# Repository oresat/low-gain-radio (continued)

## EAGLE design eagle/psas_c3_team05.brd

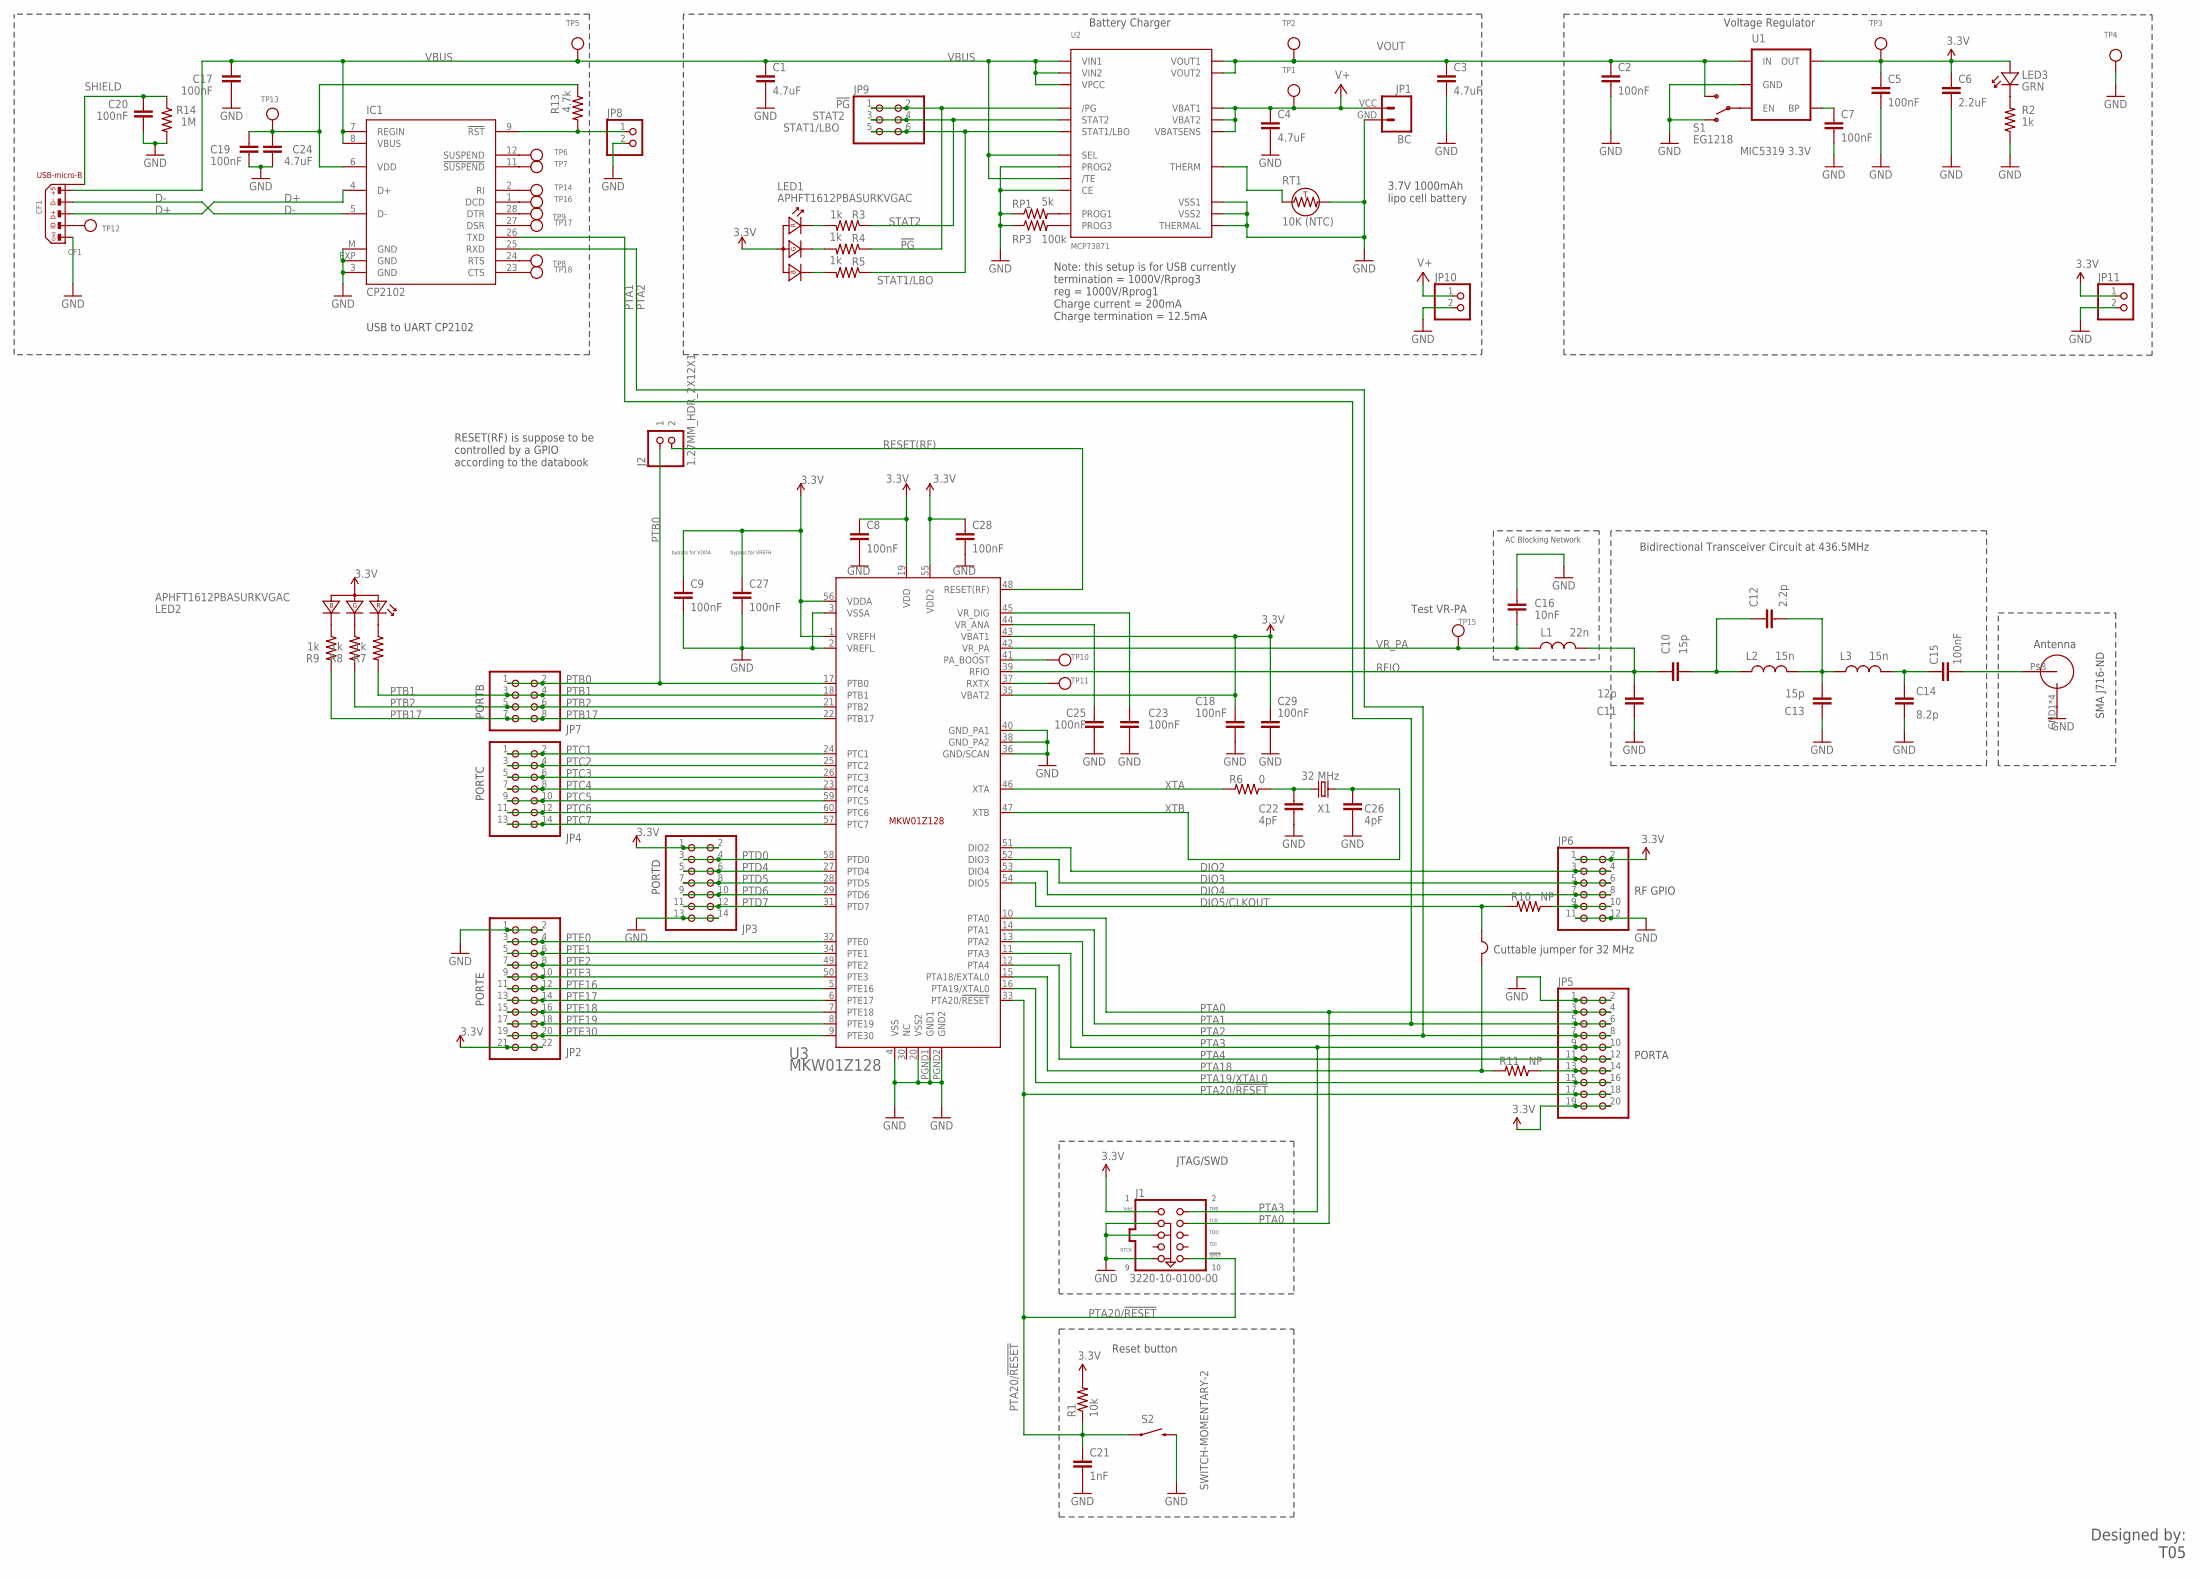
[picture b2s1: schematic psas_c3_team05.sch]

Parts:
C1, C3, C4, C24: 4.7uF; .0805-B-NOSILK
C2, C5, C7, C15, C17, C19, C20: 100nF; .0603-B-NOSILK
C6: 2.2uF; .0805-B-NOSILK
C8, C9, C18, C23, C25, C27, C28, C29: 100nF; .0603-B-NOSILK; MPN GRM188R71C104KA01D
C10, C13: 15p; .0603-B-NOSILK
C11: 12p; .0603-B-NOSILK
C12: 2.2p; .0603-B-NOSILK
C14: 8.2p; .0603-B-NOSILK
C16: 10nF; .0603-B-NOSILK
C21: 1nF; .0603-B-NOSILK
C22, C26: 4pF; .0603-B-NOSILK; MPN GRM1885C1H4R0CA01D
CF1: CF1; USB-MICRO-B-PTH-HIROSE
IC1: CP2102; MLP28
J1: 3220-10-0100-00; PINHEADER-2X5-0.05+POL+SILK
J2: 1.27MM_HDR_2X12X1; 1.27MM_2X1
JP1: BC; SPARKFUN-CONNECTORS_JST-2-SMD-VERT
JP2: PINHD-2X11; 2X11
JP3, JP4: PINHD-2X7; 2X07
JP5: PINHD-2X10; 2X10
JP6: PINHD-2X6; 2X06
JP7: PINHD-2X4; 2X04
JP8, JP10, JP11: PINHD-1X2; 1X02
JP9: PINHD-2X3; 2X03
L1: 22n; .0603-B-NOSILK
L2, L3: 15n; .0603-B-NOSILK
LED1, LED2: APHFT1612PBASURKVGAC; KINGBRITE_RGBLED_1.6X1.26
LED3: GRN; LED-0603
R1: 10k; .0603-B-NOSILK
R2, R3, R4, R5, R7, R8, R9: 1k; .0603-B-NOSILK
R6: 0; .0603-B-NOSILK
R10, R11: NP; .0603-B-NOSILK
R13: 4.7k; .0603-B-NOSILK
R14: 1M; .0603-B-NOSILK
RP1: 5k; .0603-B-NOSILK
RP3: 100k; .0603-B-NOSILK
RT1: 10K (NTC); R1206
S1: EG1218; SWITCH-SPDT
S2: SWITCH-MOMENTARY-2; TACTILE_SWITCH_TALL
TP1, TP2, TP3, TP4, TP5, TP6, TP7, TP8, TP9, TP10, TP11, TP12, TP13, TP14, TP15, TP16, TP17, TP18: TESTPOINTROUND0.5MM; TESTPOINT_ROUND_0.5MM
U1: MIC5319 3.3V; SPARKFUN-POWERIC_SOT23-5
U2: MCP73871; QFN20_4MM
U3: MKW01Z128
U$2: SMAJ716-ND
W1: CONNECTION-0.4; CONNECTION-BUTT-0.4
X1: 32 MHz; FC-12M

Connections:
3.3V: C5.1, C6.1, C8.1, C9.1, C18.1, C27.1, C28.1, C29.1, J1.1 (VDD), JP2.21, JP2.22, JP3.1, JP3.2, JP5.19, JP5.20, JP6.1, JP6.2, JP11.1, LED1.2 (COMMON_ANODE), LED2.2 (COMMON_ANODE), LED3.A, R1.2, TP3.P$1, U1.5 (OUT), U3.1 (VREFH), U3.19 (VDD), U3.35 (VBAT2), U3.43 (VBAT1), U3.55 (VDD2), U3.56 (VDDA)
!PG: JP9.1, JP9.2, R4.1, U2.P$6 (/PG)
CP2102_VDD: C19.1, C24.1, IC1.6 (VDD), R13.1, TP13.P$1
D+: CF1.3, IC1.4 (D+)
D-: CF1.2, IC1.5 (D-)
DIO2: JP6.3, JP6.4, U3.51 (DIO2)
DIO3: JP6.5, JP6.6, U3.52 (DIO3)
DIO4: JP6.7, JP6.8, U3.53 (DIO4)
DIO5-JMP: JP6.9, JP6.10, R10.1
DIO5/CLKOUT: R10.2, U3.54 (DIO5), W1.P1 (1)
GND: C1.2, C2.2, C3.2, C4.2, C5.2, C6.2, C7.2, C8.2, C9.2, C11.2, C13.2, C14.2, C16.1, C17.2, C18.2, C19.2, C20.2, C21.2, C22.2, C23.2, C24.2, C25.2, C26.2, C27.2, C28.2, C29.2, CF1.5, IC1.3 (GND), IC1.EXP (GND), IC1.M (GND), J1.3 (GND3), J1.5 (GND5), J1.9 (GND9), JP1.GND (1), JP2.1, JP2.2, JP3.13, JP3.14, JP5.1, JP5.2, JP6.11, JP6.12, JP8.2, JP10.2, JP11.2, R2.1, R14.2, RP1.1, RP3.1, RT1.2, S1.1 (O), S2.B2 (2), TP4.P$1, U1.2 (GND), U2.P$4 (PROG2), U2.P$10 (VSS1), U2.P$11 (VSS2), U2.P$17 (CE), U2.P$21 (THERMAL), U3.2 (VREFL), U3.3 (VSSA), U3.4 (VSS), U3.20 (VSS2), U3.36 (GND/SCAN), U3.38 (GND_PA2), U3.40 (GND_PA1), U3.PGND1 (GND1), U3.PGND2 (GND2), U$2.GND1 (OUTERCONDUCTOR), U$2.GND2 (OUTERCONDUCTOR), U$2.GND3 (OUTERCONDUCTOR), U$2.GND4 (OUTERCONDUCTOR)
unnamed: C7.1, U1.4 (BP)
unnamed: LED1.3 (RK), R3.2
unnamed: LED1.4 (GK), R4.2
unnamed: LED1.1 (BK), R5.2
unnamed: IC1.12 (SUSPEND), TP6.P$1
unnamed: RT1.1, U2.P$5 (THERM)
unnamed: IC1.11 (!SUSPEND), TP7.P$1
unnamed: S1.2, U1.3 (EN)
unnamed: RP1.2, U2.P$13 (PROG1)
unnamed: RP3.2, U2.P$12 (PROG3)
unnamed: IC1.24 (RTS), TP8.P$1
unnamed: C22.1, R6.1, X1.2
unnamed: TP10.P$1, U3.41 (PA_BOOST)
unnamed: TP11.P$1, U3.37 (RXTX)
unnamed: C12.1, C13.1, L2.2, L3.1
unnamed: C10.1, C12.2, L2.1
unnamed: C15.2, U$2.P$3 (CENTERCONDUCTOR)
unnamed: C14.1, C15.1, L3.2
unnamed: IC1.2 (RI), TP14.P$1
unnamed: IC1.28 (DTR), TP9.P$1
unnamed: IC1.1 (DCD), TP16.P$1
unnamed: IC1.27 (DSR), TP17.P$1
unnamed: IC1.23 (CTS), TP18.P$1
unnamed: IC1.9 (!RST), JP8.1, R13.2
unnamed: LED3.K, R2.2
unnamed: LED2.1 (BK), R9.1
unnamed: LED2.4 (GK), R8.1
unnamed: LED2.3 (RK), R7.1
unnamed: CF1.4, TP12.P$1
PTA0: J1.4 (TCK), JP5.3, JP5.4, U3.10 (PTA0)
PTA1: IC1.26 (TXD), JP5.5, JP5.6, U3.14 (PTA1)
PTA2: IC1.25 (RXD), JP5.7, JP5.8, U3.13 (PTA2)
PTA3: J1.2 (TMS), JP5.9, JP5.10, U3.11 (PTA3)
PTA4: JP5.11, JP5.12, U3.12 (PTA4)
PTA18: R11.2, U3.15 (PTA18/EXTAL0), W1.P2 (2)
PTA18-JMP: JP5.13, JP5.14, R11.1
PTA19/XTAL0: JP5.15, JP5.16, U3.16 (PTA19/XTAL0)
PTA20/!RESET: C21.1, J1.10 (SRST), JP5.17, JP5.18, R1.1, S2.A2 (1), U3.33 (PTA20/!RESET)
PTB0: J2.1, JP7.1, JP7.2, U3.17 (PTB0)
PTB1: JP7.3, JP7.4, R7.2, U3.18 (PTB1)
PTB2: JP7.5, JP7.6, R8.2, U3.21 (PTB2)
PTB17: JP7.7, JP7.8, R9.2, U3.22 (PTB17)
PTC1: JP4.1, JP4.2, U3.24 (PTC1)
PTC2: JP4.3, JP4.4, U3.25 (PTC2)
PTC3: JP4.5, JP4.6, U3.26 (PTC3)
PTC4: JP4.7, JP4.8, U3.23 (PTC4)
PTC5: JP4.9, JP4.10, U3.59 (PTC5)
PTC6: JP4.11, JP4.12, U3.60 (PTC6)
PTC7: JP4.13, JP4.14, U3.57 (PTC7)
PTD0: JP3.3, JP3.4, U3.58 (PTD0)
PTD4: JP3.5, JP3.6, U3.27 (PTD4)
PTD5: JP3.7, JP3.8, U3.28 (PTD5)
PTD6: JP3.9, JP3.10, U3.29 (PTD6)
PTD7: JP3.11, JP3.12, U3.31 (PTD7)
PTE0: JP2.3, JP2.4, U3.32 (PTE0)
PTE1: JP2.5, JP2.6, U3.34 (PTE1)
PTE2: JP2.7, JP2.8, U3.49 (PTE2)
PTE3: JP2.9, JP2.10, U3.50 (PTE3)
PTE16: JP2.11, JP2.12, U3.5 (PTE16)
PTE17: JP2.13, JP2.14, U3.6 (PTE17)
PTE18: JP2.15, JP2.16, U3.7 (PTE18)
PTE19: JP2.17, JP2.18, U3.8 (PTE19)
PTE30: JP2.19, JP2.20, U3.9 (PTE30)
RESET(RF): J2.2, U3.48 (RESET(RF))
RFIO: C10.2, C11.1, L1.2, U3.39 (RFIO)
SHIELD: C20.1, CF1.S1 (SHIELD), CF1.S2 (SHIELD), CF1.S3 (SHIELD), CF1.S4 (SHIELD), R14.1
STAT1/LBO: JP9.5, JP9.6, R5.1, U2.P$8 (STAT1/LBO)
STAT2: JP9.3, JP9.4, R3.1, U2.P$7 (STAT2)
V+: C4.1, JP1.VCC (2), JP10.1, TP1.P$1, U2.P$14 (VBAT1), U2.P$15 (VBAT2), U2.P$16 (VBATSENS)
VBUS: C1.1, C17.1, CF1.1, IC1.7 (REGIN), IC1.8 (VBUS), TP5.P$1, U2.P$2 (VPCC), U2.P$3 (SEL), U2.P$9 (/TE), U2.P$18 (VIN1), U2.P$19 (VIN2)
VOUT: C2.1, C3.1, S1.3 (S), TP2.P$1, U1.1 (IN), U2.P$1 (VOUT1), U2.P$20 (VOUT2)
VR_ANA: C25.1, U3.44 (VR_ANA)
VR_DIG: C23.1, U3.45 (VR_DIG)
VR_PA: C16.2, L1.1, TP15.P$1, U3.42 (VR_PA)
XTA: R6.2, U3.46 (XTA)
XTB: C26.1, U3.47 (XTB), X1.1

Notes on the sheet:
Note: this setup is for USB currently termination = 1000V/Rprog3 reg = 1000V/Rprog1 Charge current = 200mA Charge termination = 12.5mA
Voltage Regulator
Battery Charger
Designed by: T05
AC Blocking Network
Bidirectional Transceiver Circuit at 436.5MHz
USB to UART CP2102
JTAG/SWD
Reset button
3.7V 1000mAh lipo cell battery
RESET(RF) is suppose to be controlled by a GPIO according to the databook
PORTC
PORTB
PORTD
PORTE
Cuttable jumper for 32 MHz
bypass for VDDA
bypass for VREFH
Antenna
SMA J716-ND
Test VR-PA
PORTA
RF GPIO

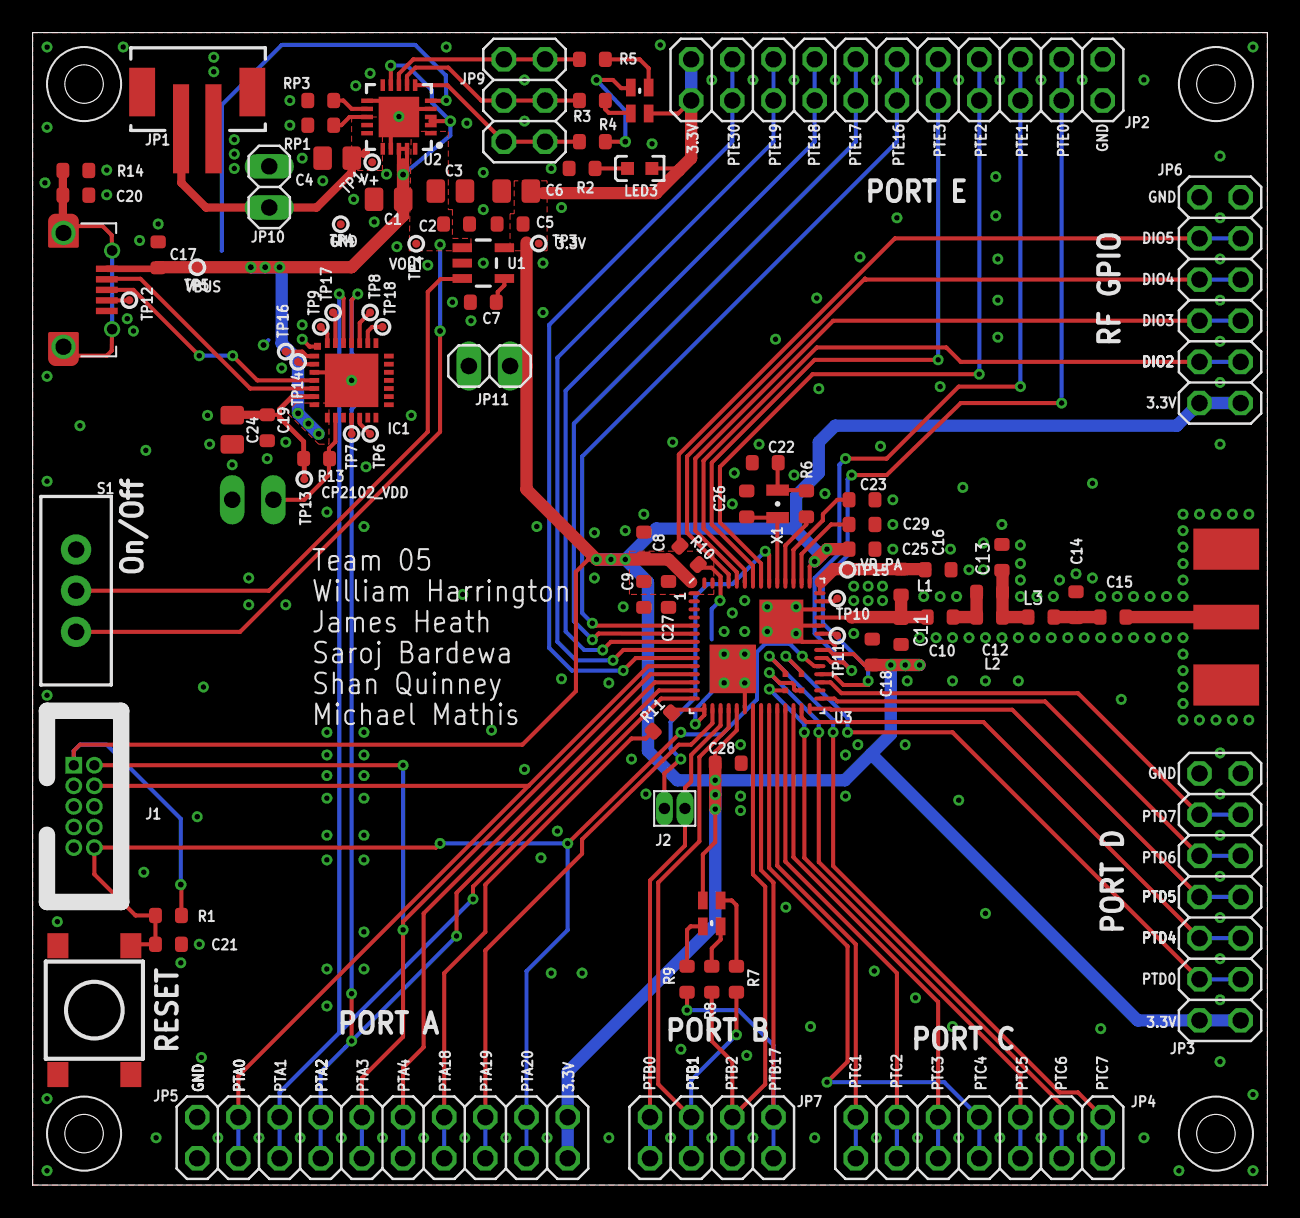
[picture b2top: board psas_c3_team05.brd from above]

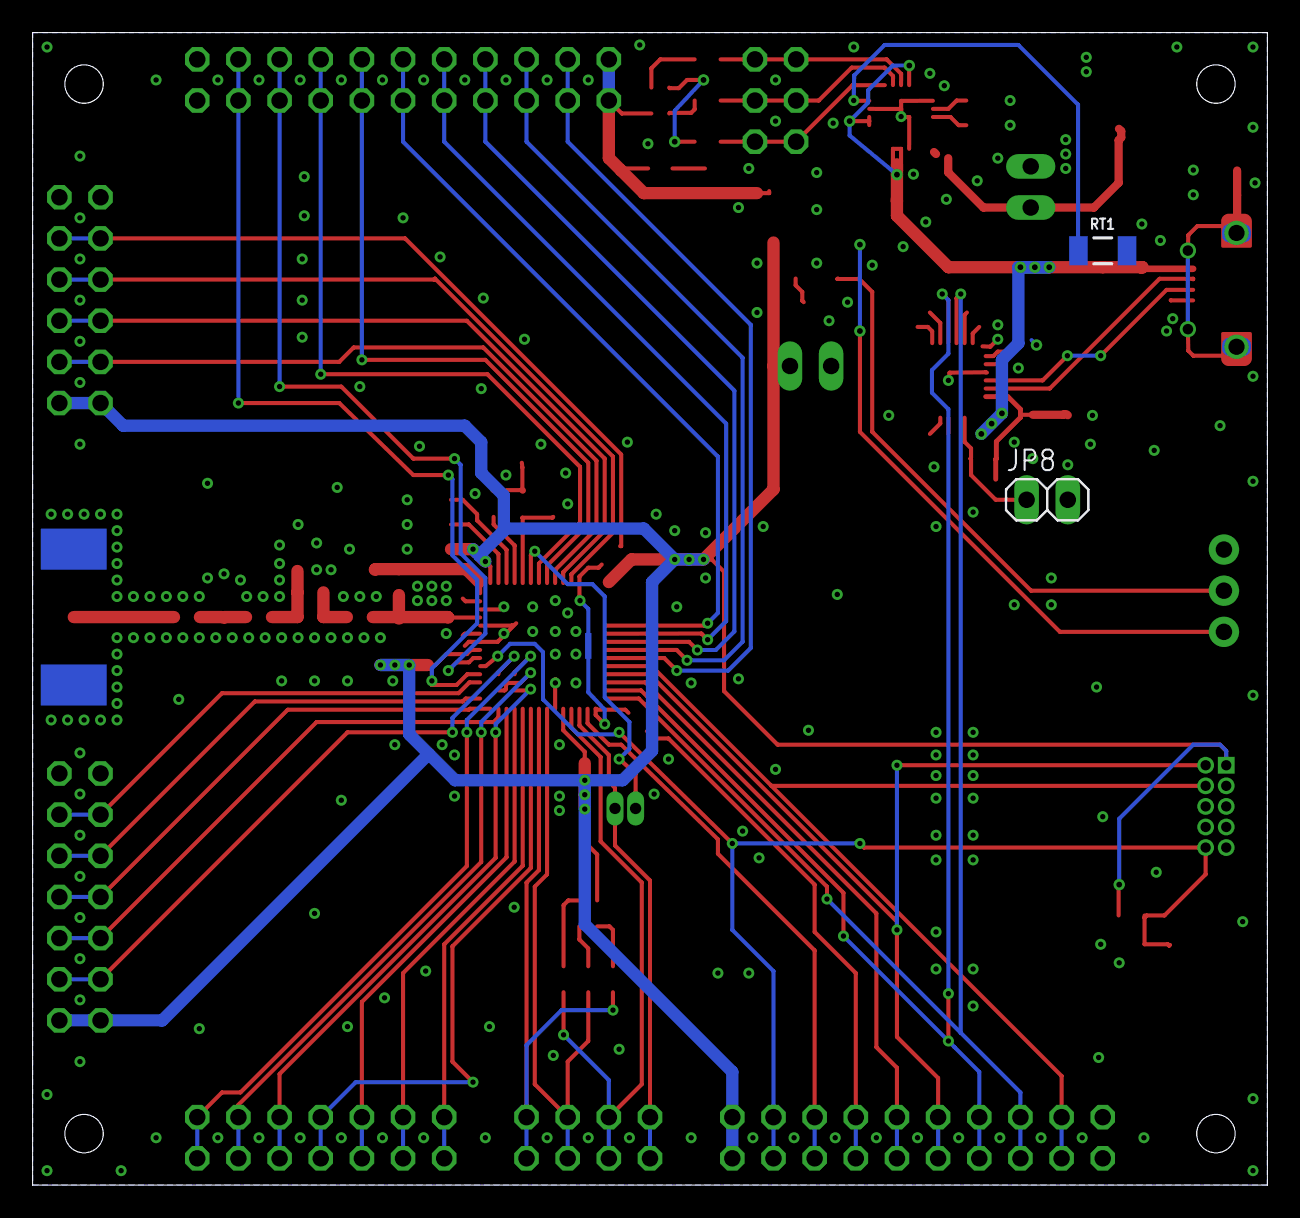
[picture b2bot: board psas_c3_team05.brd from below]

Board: 2 copper layers, 76.2 x 71.1 mm, 96 parts (3 on the bottom side), 87 nets.

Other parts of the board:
DI1, DI2, DI3, DI4: #2/.750-BARE

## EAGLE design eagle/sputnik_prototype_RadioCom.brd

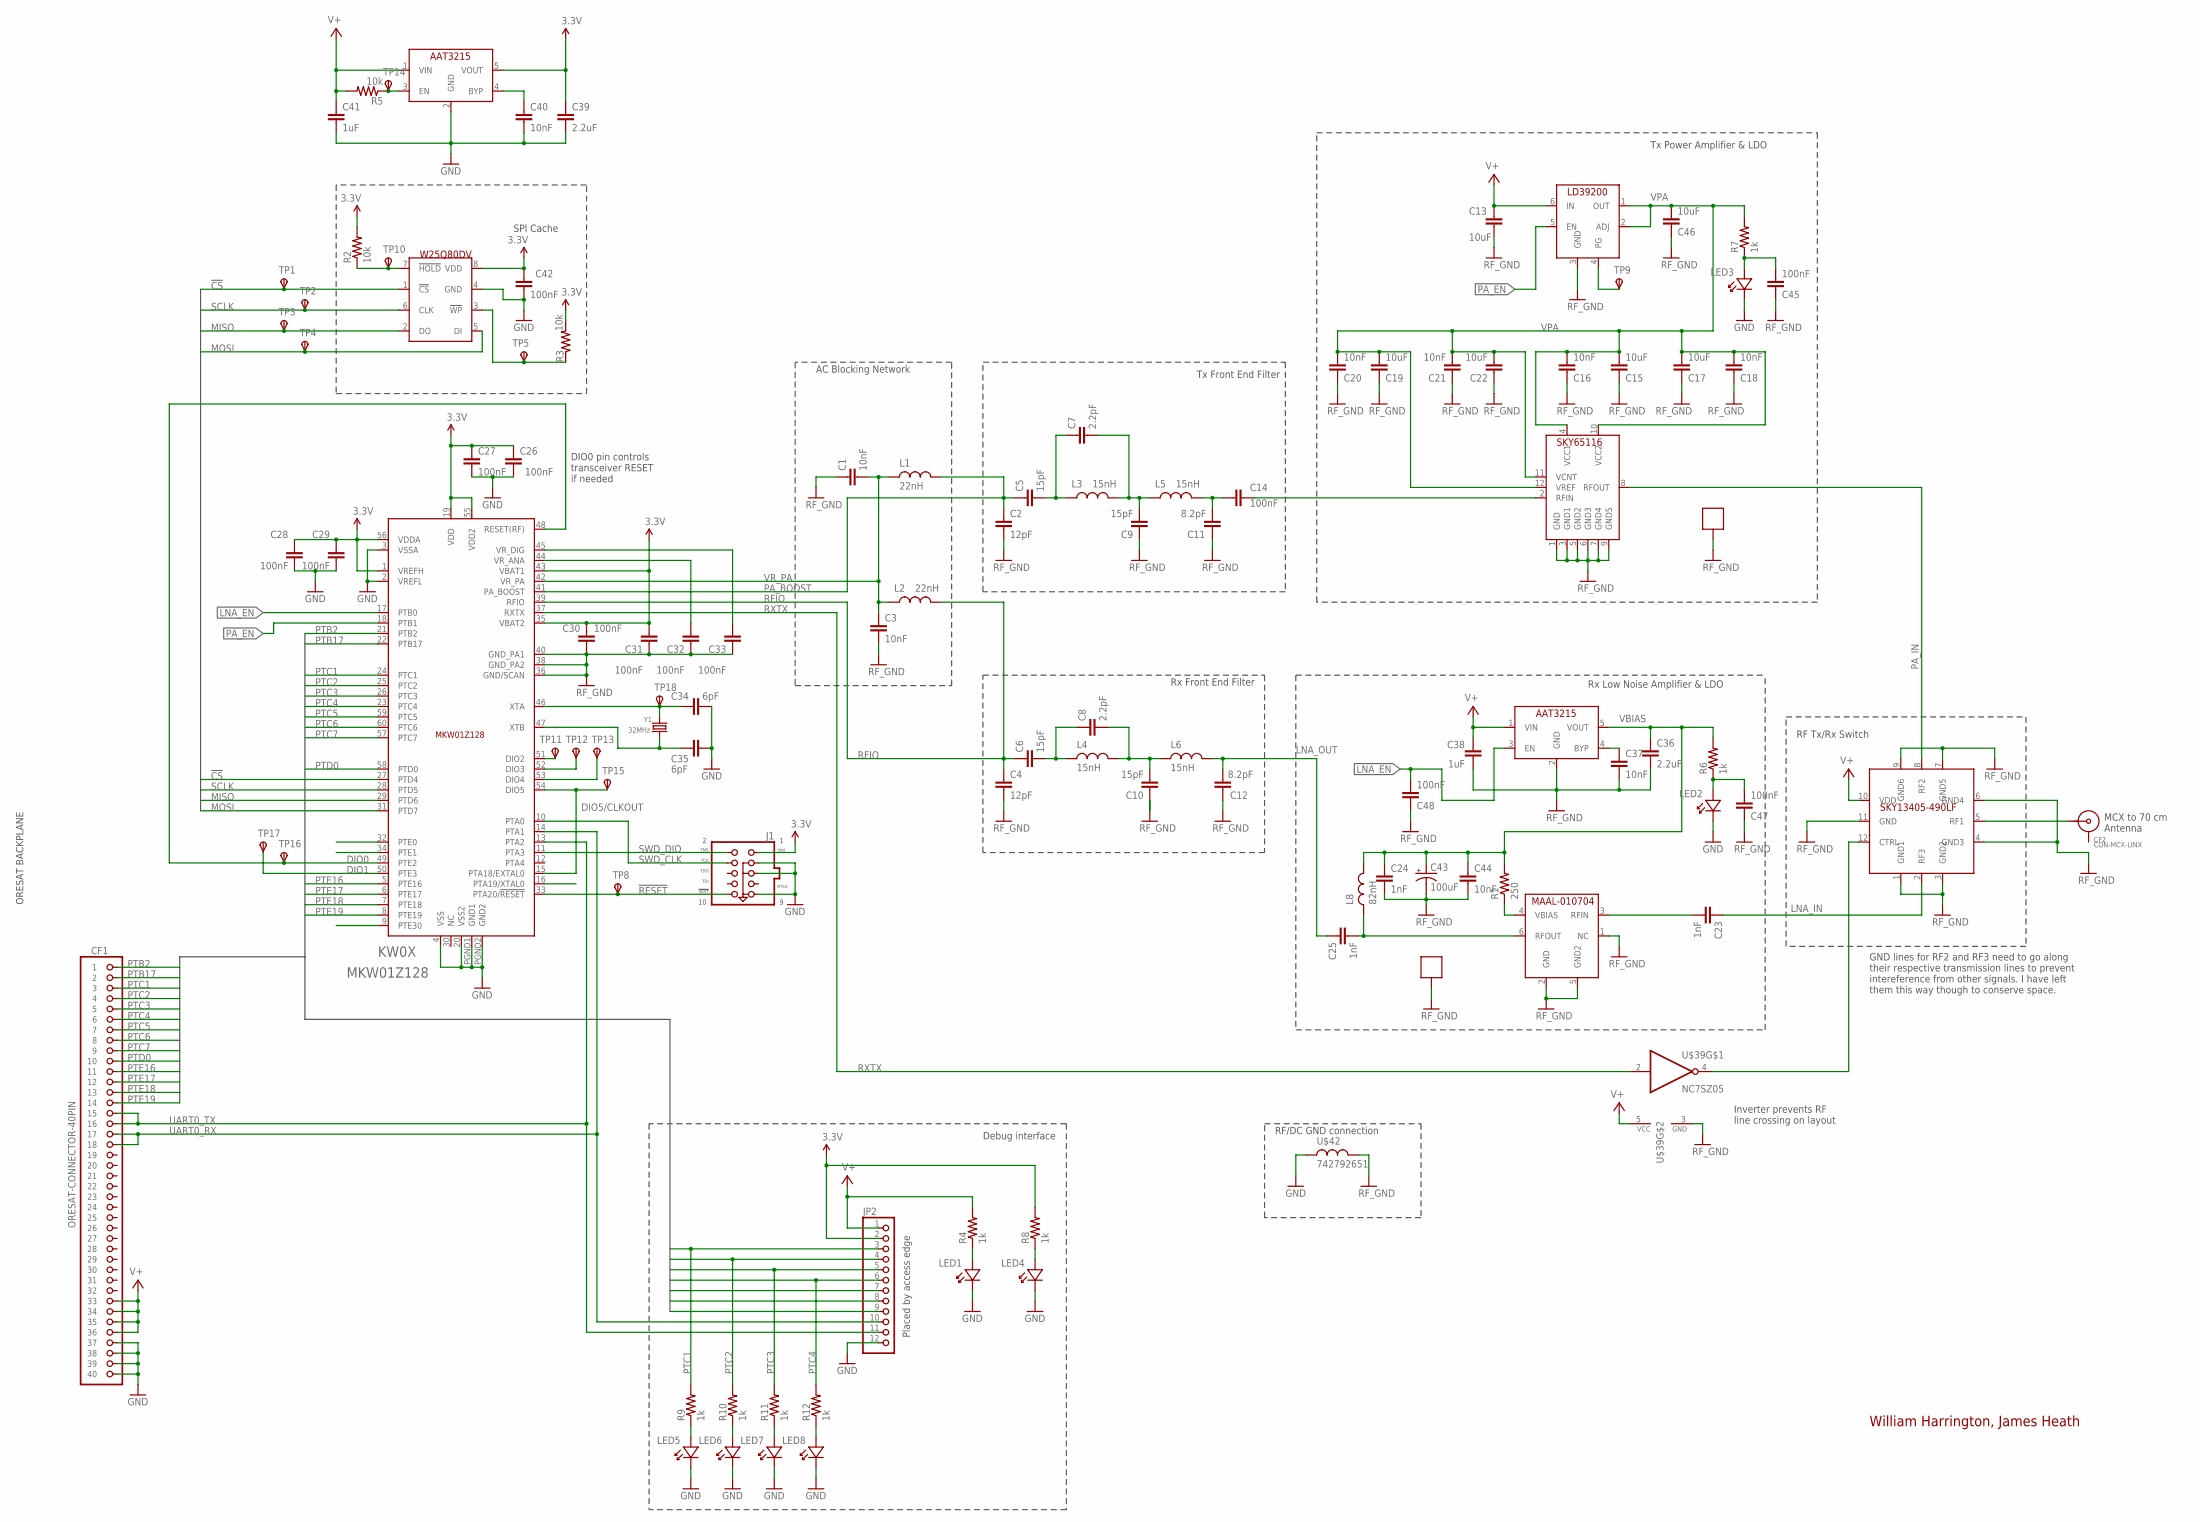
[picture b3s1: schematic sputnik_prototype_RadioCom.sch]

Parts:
C1, C3, C16, C18, C20, C21: 10nF; .0603-B-NOSILK
C2, C4: 12pF; .0603-B-NOSILK
C5, C6, C9, C10: 15pF; .0603-B-NOSILK
C7, C8: 2.2pF; .0603-B-NOSILK
C11, C12: 8.2pF; .0603-B-NOSILK
C13, C15, C17, C19, C22, C46: 10uF; .0603-B-NOSILK
C14, C26, C27, C28, C29, C30, C31, C32, C33, C42, C45, C47, C48: 100nF; .0603-B-NOSILK
C23, C24, C25: 1nF; .0402-B-NOSILK
C34, C35: 6pF; .0603-B-NOSILK
C36, C39: 2.2uF; .0402-B-NOSILK
C37, C40, C44: 10nF; .0402-B-NOSILK
C38, C41: 1uF; .0402-B-NOSILK
C43: 100uF; CT6032
CF1: ORESAT-CONNECTOR-40PIN; HARWIN-ARCHER-M50-3202045
CF2: CON-MCX-LINX; CON-MCX-LINX-CONMCX003.062
J1: JTAG_ARM-10-50MIL; PINHEADER-2X5-0.05+POL+SILK
JP2: PINHD-1X12; 1X12
KW0X: MKW01Z128; MPN MKW01Z128CHN
L1, L2: 22nH; .0603-B-NOSILK
L3, L4, L5, L6: 15nH; .0603-B-NOSILK
L8: 82nH; .0603-B-NOSILK
LED1, LED2, LED3, LED4, LED5, LED6, LED7, LED8: LED-0603
LNA: MAAL-010704; MPN MAAL-010704-TR3000
PA: SKY65116; MPN SKY65116
R1: 250; .0603-B-NOSILK
R2, R3, R5: 10k; .0603-B-NOSILK
R4, R6, R7, R8, R9, R10, R11, R12: 1k; .0603-B-NOSILK
SH1, SH2: BMI-S-202-SHIELD; BMI-S-202
TP1, TP2, TP3, TP4, TP5, TP8, TP9, TP10, TP11, TP12, TP13, TP14, TP15, TP16, TP17, TP18: TPSPAD1-13; P1-13
TRSWITCH: SKY13405-490LF; MPN SKY13405-490LF
U$1: W25Q80DV
U$7, U$8: AAT3215
U$9: LD39200
U$39: NC7SZ05
U$42: 742792651; .0603-B-NOSILK
Y1: 32MHz; CRYSTAL_2.5X2; MPN FA20H 32.0000MF12Y-W3

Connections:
3.3V: C26.1, C27.1, C28.2, C29.2, C30.2, C31.2, C39.1, C42.2, J1.1 (VDD), JP2.2, KW0X.1 (VREFH), KW0X.19 (VDD), KW0X.35 (VBAT2), KW0X.43 (VBAT1), KW0X.55 (VDD2), KW0X.56 (VDDA), R2.2, R3.2, R8.2, U$1.8 (VDD), U$8.5 (VOUT)
!CS: KW0X.27 (PTD4), TP1.TP, U$1.1 (!CS)
!HOLD: R2.1, TP10.TP, U$1.7 (!HOLD)
!RESET: J1.10 (SRST), KW0X.33 (PTA20/!RESET), TP8.TP
ASD: C47.1
DIO0: KW0X.48 (RESET(RF)), KW0X.49 (PTE2), TP16.TP
DIO1: KW0X.50 (PTE3), TP17.TP
DIO5/CLKOUT: KW0X.15 (PTA18/EXTAL0), KW0X.54 (DIO5), TP15.TP
GND: C26.2, C27.2, C28.1, C29.1, C34.1, C35.1, C36.2, C37.2, C38.2, C39.2, C40.2, C41.2, C42.1, C48.1, CF1.P$37 (37), CF1.P$38 (38), CF1.P$39 (39), CF1.P$40 (40), J1.3 (GND3), J1.5 (GND5), J1.9 (GND9), JP2.12, KW0X.2 (VREFL), KW0X.3 (VSSA), KW0X.4 (VSS), KW0X.20 (VSS2), KW0X.PGND1 (GND1), KW0X.PGND2 (GND2), LED1.K, LED2.K, LED3.K, LED4.K, LED5.K, LED6.K, LED7.K, LED8.K, LNA.1 (NC), TRSWITCH.11 (GND), U$1.4 (GND), U$7.2 (GND), U$8.2 (GND), U$42.1
LNA_EN: C48.2, KW0X.17 (PTB0), U$7.3 (EN)
LNA_IN: C23.1, TRSWITCH.2 (RF3)
LNA_OUT: C12.2, C25.1, L6.2
MISO: KW0X.29 (PTD6), TP3.TP, U$1.2 (DO)
MOSI: KW0X.31 (PTD7), TP4.TP, U$1.5 (DI)
unnamed: C37.1, U$7.4 (BYP)
unnamed: TRSWITCH.12 (CTRL), U$39.4 (OUT)
unnamed: KW0X.51 (DIO2), TP11.TP
unnamed: TP9.TP, U$9.4 (PG)
unnamed: KW0X.52 (DIO3), TP12.TP
unnamed: C34.2, KW0X.46 (XTA), TP18.TP, Y1.1
unnamed: C25.2, L8.1, LNA.6 (RFOUT)
unnamed: C35.2, KW0X.47 (XTB), Y1.3 (2)
unnamed: KW0X.53 (DIO4), TP13.TP
unnamed: C5.2, C7.1, L3.1
unnamed: R3.1, TP5.TP, U$1.3 (!WP)
unnamed: R5.1, TP14.TP, U$8.3 (EN)
unnamed: C40.1, U$8.4 (BYP)
unnamed: LED1.A, R4.1
unnamed: LED5.A, R9.1
unnamed: C7.2, C9.2, L3.2, L5.1
unnamed: C11.2, C14.2, L5.2
unnamed: C6.2, C8.1, L4.1
unnamed: C8.2, C10.2, L4.2, L6.1
unnamed: LED6.A, R10.1
unnamed: LED7.A, R11.1
unnamed: LED4.A, R8.1
unnamed: LED8.A, R12.1
unnamed: C23.2, LNA.3 (RFIN)
unnamed: LNA.4 (VBIAS), R1.1
unnamed: CF2.CENTER, TRSWITCH.5 (RF1)
unnamed: C32.2, KW0X.44 (VR_ANA)
unnamed: C33.2, KW0X.45 (VR_DIG)
unnamed: C14.1, PA.2 (RFIN)
PA_BOOST: C2.1, C5.1, KW0X.41 (PA_BOOST), L1.2
PA_EN: KW0X.18 (PTB1), U$9.5 (EN)
PA_IN: PA.8 (RFOUT), TRSWITCH.8 (RF2)
PTA19: KW0X.16 (PTA19/XTAL0)
PTB2: CF1.P$1 (1), KW0X.21 (PTB2)
PTB17: CF1.P$2 (2), KW0X.22 (PTB17)
PTC1: CF1.P$3 (3), JP2.3, KW0X.24 (PTC1), R9.2
PTC2: CF1.P$4 (4), JP2.4, KW0X.25 (PTC2), R10.2
PTC3: CF1.P$5 (5), JP2.5, KW0X.26 (PTC3), R11.2
PTC4: CF1.P$6 (6), JP2.6, KW0X.23 (PTC4), R12.2
PTC5: CF1.P$7 (7), JP2.7, KW0X.59 (PTC5)
PTC6: CF1.P$8 (8), JP2.8, KW0X.60 (PTC6)
PTC7: CF1.P$9 (9), JP2.9, KW0X.57 (PTC7)
PTD0: CF1.P$10 (10), KW0X.58 (PTD0)
PTE0: KW0X.32 (PTE0)
PTE1: KW0X.34 (PTE1)
PTE16: CF1.P$11 (11), KW0X.5 (PTE16)
PTE17: CF1.P$12 (12), KW0X.6 (PTE17)
PTE18: CF1.P$13 (13), KW0X.7 (PTE18)
PTE19: CF1.P$14 (14), KW0X.8 (PTE19)
PTE30: KW0X.9 (PTE30)
RFIO: C4.1, C6.1, KW0X.39 (RFIO), L2.2
RF_GND: C1.1, C2.2, C3.2, C4.2, C9.1, C10.1, C11.1, C12.1, C13.1, C15.1, C16.1, C17.1, C18.1, C19.1, C20.1, C21.1, C22.1, C24.2, C30.1, C31.1, C32.1, C33.1, C43.-, C44.2, C45.1, C46.1, KW0X.36 (GND/SCAN), KW0X.38 (GND_PA2), KW0X.40 (GND_PA1), LNA.2 (GND), LNA.5 (GND2), PA.1 (GND), PA.3 (GND1), PA.5 (GND2), PA.6 (GND3), PA.7 (GND4), PA.9 (GND5), SH1.P$1, SH1.P$2, SH1.P$3, SH1.P$4, SH1.P$5, SH1.P$6, SH1.P$7, SH1.P$8, SH1.P$9, SH1.P$10, SH1.P$11, SH1.P$12, SH2.P$1, SH2.P$2, SH2.P$3, SH2.P$4, SH2.P$5, SH2.P$6, SH2.P$7, SH2.P$8, SH2.P$9, SH2.P$10, SH2.P$11, SH2.P$12, TRSWITCH.1 (GND1), TRSWITCH.3 (GND2), TRSWITCH.4 (GND3), TRSWITCH.6 (GND4), TRSWITCH.7 (GND5), TRSWITCH.9 (GND6), U$9.3 (GND), U$39.3 (GND), U$42.2
RXTX: KW0X.37 (RXTX), U$39.2 (IN)
SCLK: KW0X.28 (PTD5), TP2.TP, U$1.6 (CLK)
SWD_CLK: J1.4 (TCK), KW0X.10 (PTA0)
SWD_DIO: J1.2 (TMS), KW0X.11 (PTA3)
UART0_RX: CF1.P$17 (17), CF1.P$18 (18), JP2.10, KW0X.14 (PTA1)
UART0_TX: CF1.P$15 (15), CF1.P$16 (16), JP2.11, KW0X.13 (PTA2)
V+: C13.2, C38.1, C41.1, CF1.P$33 (33), CF1.P$34 (34), CF1.P$35 (35), CF1.P$36 (36), JP2.1, R4.2, R5.2, TRSWITCH.10 (VDD), U$7.1 (VIN), U$8.1 (VIN), U$9.6 (IN), U$39.5 (VCC)
VBIAS: C24.1, C36.1, C43.+, C44.1, L8.2, R1.2, R6.2, U$7.5 (VOUT)
VPA: C15.2, C16.2, C17.2, C18.2, C19.2, C20.2, C21.2, C22.2, C46.2, PA.4 (VCC1), PA.10 (VCC2), PA.11 (VCNT), PA.12 (VREF), R7.2, U$9.1 (OUT), U$9.2 (ADJ)
VR_PA: C1.2, C3.1, KW0X.42 (VR_PA), L1.1, L2.1
V_LNA_FILTERED: C47.2, LED2.A, R6.1
V_PA_FILTERED: C45.2, LED3.A, R7.1

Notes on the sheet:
William Harrington, James Heath
AC Blocking Network
Tx Front End Filter
Tx Power Amplifier & LDO
Rx Front End Filter
Rx Low Noise Amplifier & LDO
RF Tx/Rx Switch
MCX to 70 cm Antenna
GND lines for RF2 and RF3 need to go along their respective transmission lines to prevent intereference from other signals. I have left them this way though to conserve space.
SPI Cache
RF/DC GND connection
Debug interface
Placed by access edge
ORESAT BACKPLANE
DIO0 pin controls transceiver RESET if needed
Inverter prevents RF line crossing on layout

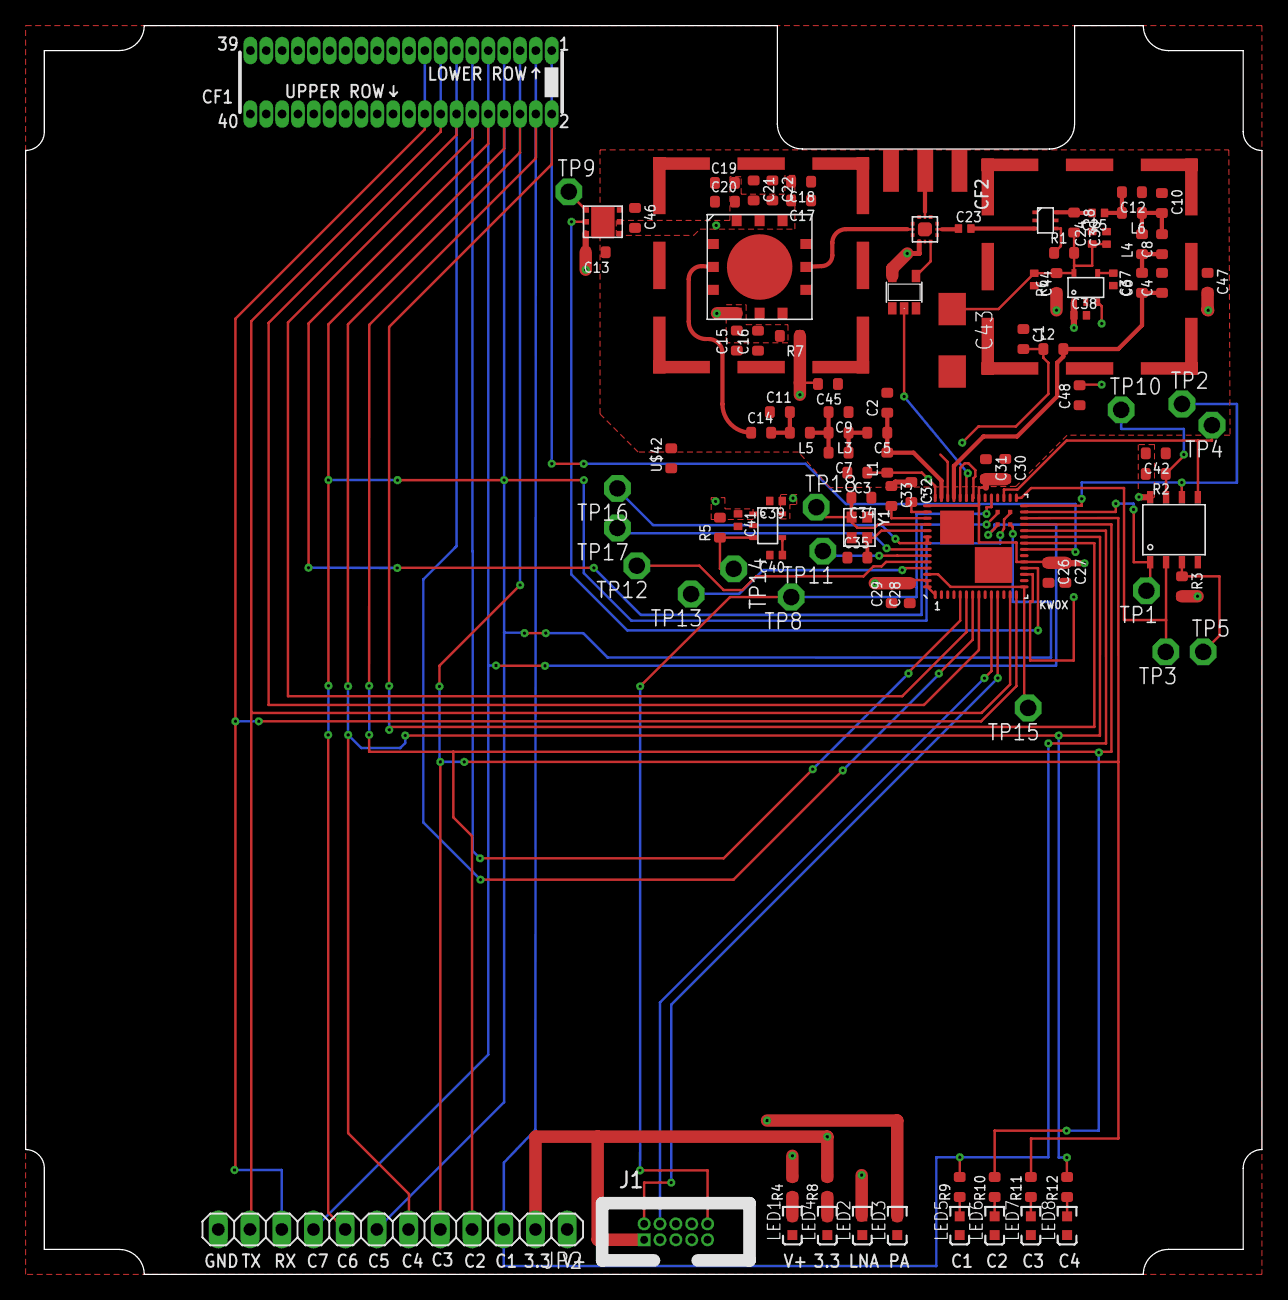
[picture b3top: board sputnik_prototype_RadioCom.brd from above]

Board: 4 copper layers, 99.0 x 100.0 mm, 109 parts (0 on the bottom side), 73 nets.

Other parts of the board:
U$35: ORESAT-CARD-RF-V0.3
